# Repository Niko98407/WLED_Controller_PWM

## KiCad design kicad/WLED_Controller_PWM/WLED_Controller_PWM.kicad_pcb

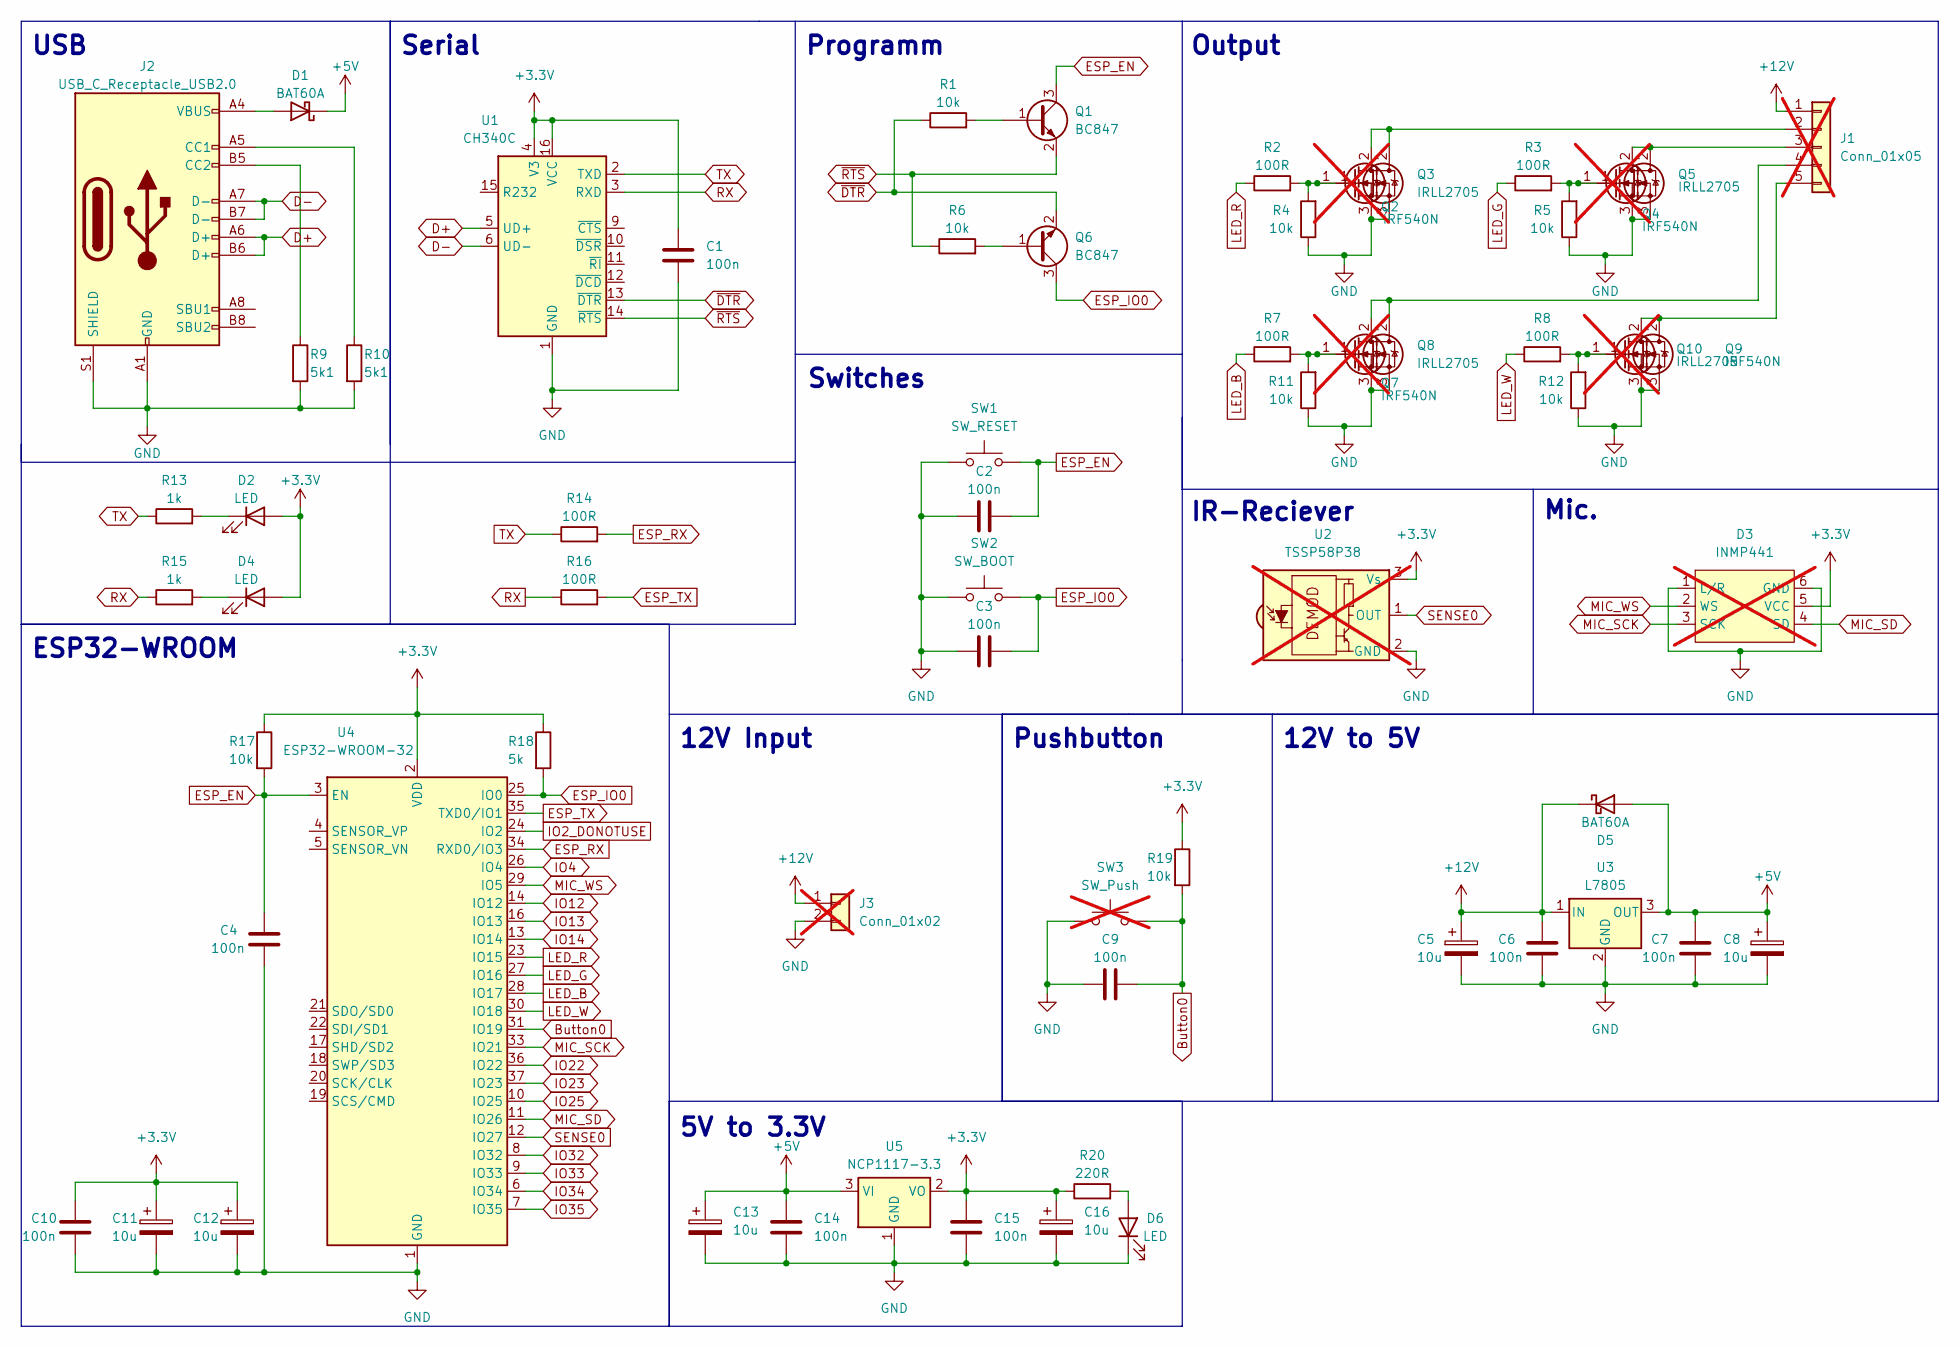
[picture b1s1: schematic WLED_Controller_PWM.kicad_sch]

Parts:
C1, C2, C3, C4, C6, C7, C9, C10, C14, C15: 100n; C_0603_1608Metric_Pad1.08x0.95mm_HandSolder
C5, C8, C11, C12, C13, C16: 10u; CP_EIA-3216-18_Kemet-A_Pad1.58x1.35mm_HandSolder; LCSC C7177
D1: BAT60A; D_SOD-323_HandSoldering; LCSC C124187
D2, D4, D6: LED; LED_0603_1608Metric_Pad1.05x0.95mm_HandSolder
D3: INMP441; INMP441_Module; not fitted
D5: BAT60A; D_SOD-323_HandSoldering
J1: Conn_01x05; WAGO_250-205_1x05_P3.50mm; not fitted
J2: USB_C_Receptacle_USB2.0; USB_C; LCSC C2760486
J3: Conn_01x02; WAGO_250-202_1x02_P3.50mm; not fitted
Q1, Q6: BC847; SOT-23
Q2, Q4, Q7, Q9: IRF540N; TO-220-3_Vertical; not fitted
Q3, Q5, Q8, Q10: IRLL2705; SOT-223; LCSC C151552
R1, R4, R5, R6, R11, R12, R17, R19: 10k; R_0603_1608Metric_Pad0.98x0.95mm_HandSolder
R2, R3, R7, R8, R14, R16: 100R; R_0603_1608Metric_Pad0.98x0.95mm_HandSolder
R9, R10: 5k1; R_0603_1608Metric_Pad0.98x0.95mm_HandSolder
R13, R15: 1k; R_0603_1608Metric_Pad0.98x0.95mm_HandSolder
R18: 5k; R_0603_1608Metric_Pad0.98x0.95mm_HandSolder
R20: 220R; R_0603_1608Metric_Pad0.98x0.95mm_HandSolder
SW1: SW_RESET; SW_SPST_B3U-1000P; LCSC C843669
SW2: SW_BOOT; SW_SPST_B3U-1000P; LCSC C843669
SW3: SW_Push; SW_PUSH_6mm_H13mm; not fitted
U1: CH340C; SOIC-16_3.9x9.9mm_P1.27mm; LCSC C84681
U2: TSSP58P38; TO-92L_HandSolder; not fitted
U3: L7805; TO-263-3_TabPin2; LCSC C507146
U4: ESP32-WROOM-32; LCSC C82899
U5: NCP1117-3.3; SOT-223-3_TabPin2; LCSC C369933

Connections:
+3.3V: C1.1, C10.1, C11.1, C12.1, C15.1, C16.1, D2.2 (A), D3.5 (VCC), D4.2 (A), R17.1, R18.1, R19.1, R20.1, U1.4 (V3), U1.16 (VCC), U2.3 (Vs), U4.2 (VDD), U5.2 (VO)
+5V: C7.1, C8.1, C13.1, C14.1, D1.1 (K), D5.2 (A), U3.3 (OUT), U5.3 (VI)
+12V: C5.1, C6.1, D5.1 (K), J1.1, J3.1, U3.1 (IN)
Button0: C9.2, R19.2, SW3.2, U4.31 (IO19)
D+: J2.A6 (D+), J2.B6 (D+), U1.5 (UD+)
D-: J2.A7 (D-), J2.B7 (D-), U1.6 (UD-)
ESP_EN: C2.2, C4.1, Q1.3 (C), R17.2, SW1.2, U4.3 (EN)
ESP_IO0: C3.2, Q6.3 (C), R18.2, SW2.2, U4.25 (IO0)
ESP_RX: R14.2, U4.34 (RXD0/IO3)
ESP_TX: R16.2, U4.35 (TXD0/IO1)
GND: C1.2, C2.1, C3.1, C4.2, C5.2, C6.2, C7.2, C8.2, C9.1, C10.2, C11.2, C12.2, C13.2, C14.2, C15.2, C16.2, D3.1 (L/R), D3.6 (GND), D6.1 (K), J2.A1 (GND), J2.A12 (GND), J2.B1 (GND), J2.B12 (GND), J2.S1 (SHIELD), J3.2, Q2.3 (S), Q3.3 (S), Q4.3 (S), Q5.3 (S), Q7.3 (S), Q8.3 (S), Q9.3 (S), Q10.3 (S), R4.1, R5.1, R9.2, R10.2, R11.1, R12.1, SW1.1, SW2.1, SW3.1, U1.1 (GND), U2.2 (GND), U3.2 (GND), U4.1 (GND), U4.15 (GND), U4.38 (GND), U4.39 (GND), U5.1 (GND)
IO2_DONOTUSE: U4.24 (IO2)
IO4: U4.26 (IO4)
IO12: U4.14 (IO12)
IO13: U4.16 (IO13)
IO14: U4.13 (IO14)
IO22: U4.36 (IO22)
IO23: U4.37 (IO23)
IO25: U4.10 (IO25)
IO32: U4.8 (IO32)
IO33: U4.9 (IO33)
IO34: U4.6 (IO34)
IO35: U4.7 (IO35)
LED_B: R7.1, U4.28 (IO17)
LED_G: R3.1, U4.27 (IO16)
LED_R: R2.1, U4.23 (IO15)
LED_W: R8.1, U4.30 (IO18)
MIC_SCK: D3.3 (SCK), U4.33 (IO21)
MIC_SD: D3.4 (SD), U4.11 (IO26)
MIC_WS: D3.2 (WS), U4.29 (IO5)
unnamed: D1.2 (A), J2.A4 (VBUS), J2.A9 (VBUS), J2.B4 (VBUS), J2.B9 (VBUS)
unnamed: D2.1 (K), R13.2
unnamed: D4.1 (K), R15.2
unnamed: D6.2 (A), R20.2
unnamed: J1.2, Q2.2 (D), Q3.2 (D)
unnamed: J1.3, Q4.2 (D), Q5.2 (D)
unnamed: J1.4, Q7.2 (D), Q8.2 (D)
unnamed: J1.5, Q9.2 (D), Q10.2 (D)
unnamed: J2.A5 (CC1), R10.1
unnamed: J2.B5 (CC2), R9.1
unnamed: Q1.1 (B), R1.2
unnamed: Q2.1 (G), Q3.1 (G), R2.2, R4.2
unnamed: Q4.1 (G), Q5.1 (G), R3.2, R5.2
unnamed: Q6.1 (B), R6.2
unnamed: Q7.1 (G), Q8.1 (G), R7.2, R11.2
unnamed: Q9.1 (G), Q10.1 (G), R8.2, R12.2
RX: R15.1, R16.1, U1.3 (RXD)
SENSE0: U2.1 (OUT), U4.12 (IO27)
TX: R13.1, R14.1, U1.2 (TXD)
~DTR: Q6.2 (E), R1.1, U1.13 (~DTR)
~RTS: Q1.2 (E), R6.1, U1.14 (~RTS)

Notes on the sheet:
USB
Switches
12V Input
Serial
Output
IR-Reciever
Mic.
ESP32-WROOM
Programm
Pushbutton
5V to 3.3V
12V to 5V

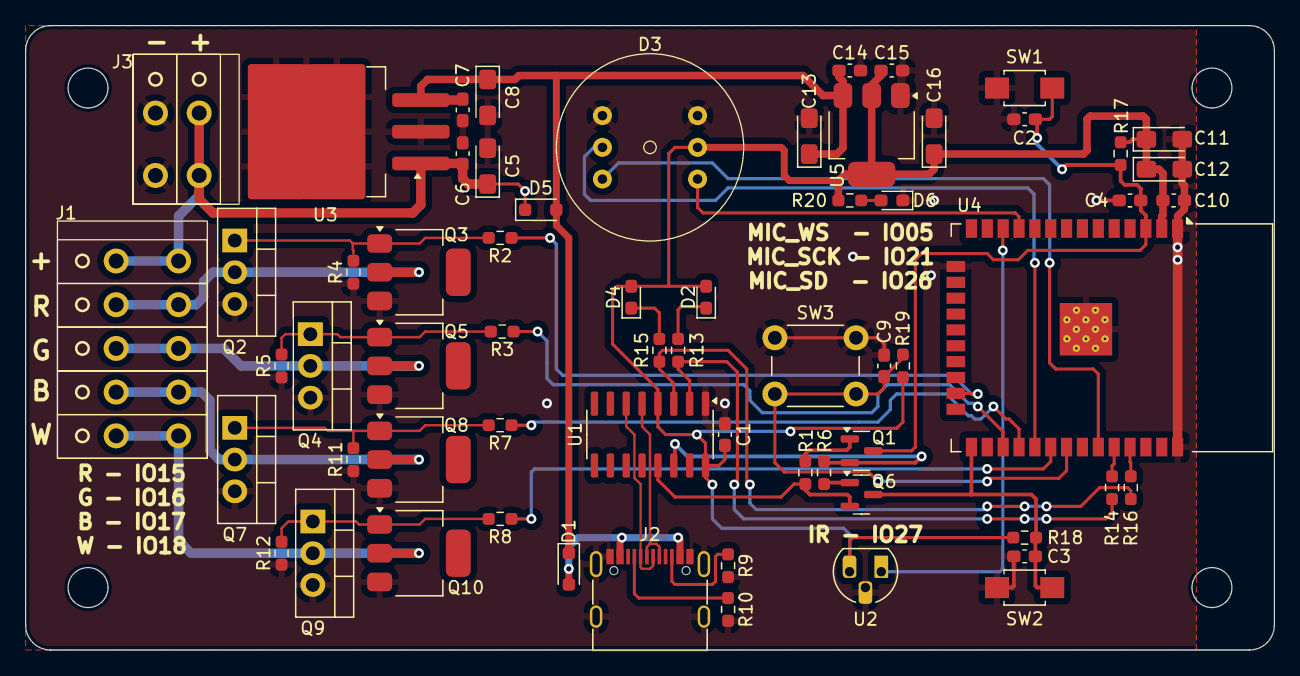
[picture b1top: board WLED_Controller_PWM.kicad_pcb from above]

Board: 2 copper layers, 100.0 x 50.0 mm, 63 parts (0 on the bottom side), 39 nets.

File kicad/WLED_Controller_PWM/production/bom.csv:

Designator,Footprint,Quantity,Value,LCSC Part #
"C1, C10, C14, C15, C2, C3, C4, C6, C7, C9",0603,10,100n,
"C11, C12, C13, C16, C5, C8",CP_EIA-3216-18_Kemet-A_Pad1.58x1.35mm_HandSolder,6,10u,C7177
D1,D_SOD-323_HandSoldering,1,BAT60A,C124187
"D2, D4, D6",0603,3,LED,
D5,D_SOD-323_HandSoldering,1,BAT60A,
J2,USB_C,1,USB_C_Receptacle_USB2.0,C2760486
"Q1, Q6",SOT-23,2,BC847,
"Q10, Q3, Q5, Q8",SOT-223,4,IRLL2705,C151552
"R1, R11, R12, R17, R19, R4, R5, R6",0603,8,10k,
"R10, R9",0603,2,5k1,
"R13, R15",0603,2,1k,
"R14, R16, R2, R3, R7, R8",0603,6,100R,
R18,0603,1,5k,
R20,0603,1,220R,
SW1,SW_SPST_B3U-1000P,1,SW_RESET,C843669
SW2,SW_SPST_B3U-1000P,1,SW_BOOT,C843669
U1,SOIC-16_3.9x9.9mm_P1.27mm,1,CH340C,C84681
U3,TO-263-3_TabPin2,1,L7805,C507146
U4,ESP32-WROOM-32,1,ESP32-WROOM-32,C82899
U5,SOT-223-3_TabPin2,1,NCP1117-3.3,C369933

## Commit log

2024-03-10 setup repo
    Starting with a copy of the other WLED Project
2024-03-11 Add PWM Controllers
2024-03-12 add 7805
2024-04-28 Change to WAGO250
2024-05-03 Add V1R1
2024-05-04 recreate gerber files
2024-05-05 add bom
2024-05-22 change mosfet
2025-02-08 Do Not Place FETS
2025-02-09 Add new PCB-Layout
